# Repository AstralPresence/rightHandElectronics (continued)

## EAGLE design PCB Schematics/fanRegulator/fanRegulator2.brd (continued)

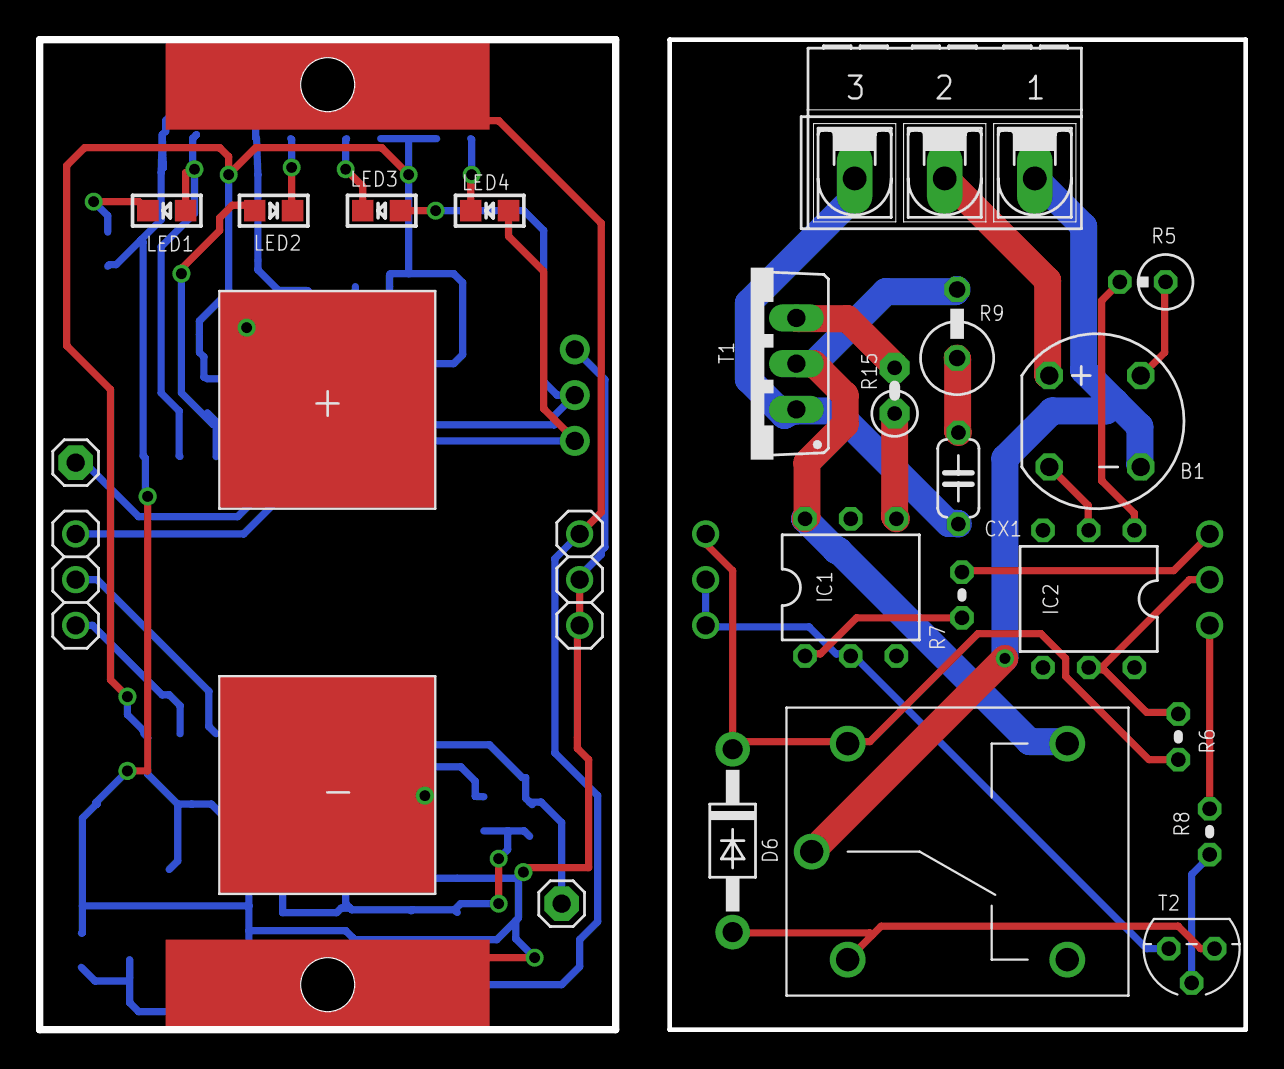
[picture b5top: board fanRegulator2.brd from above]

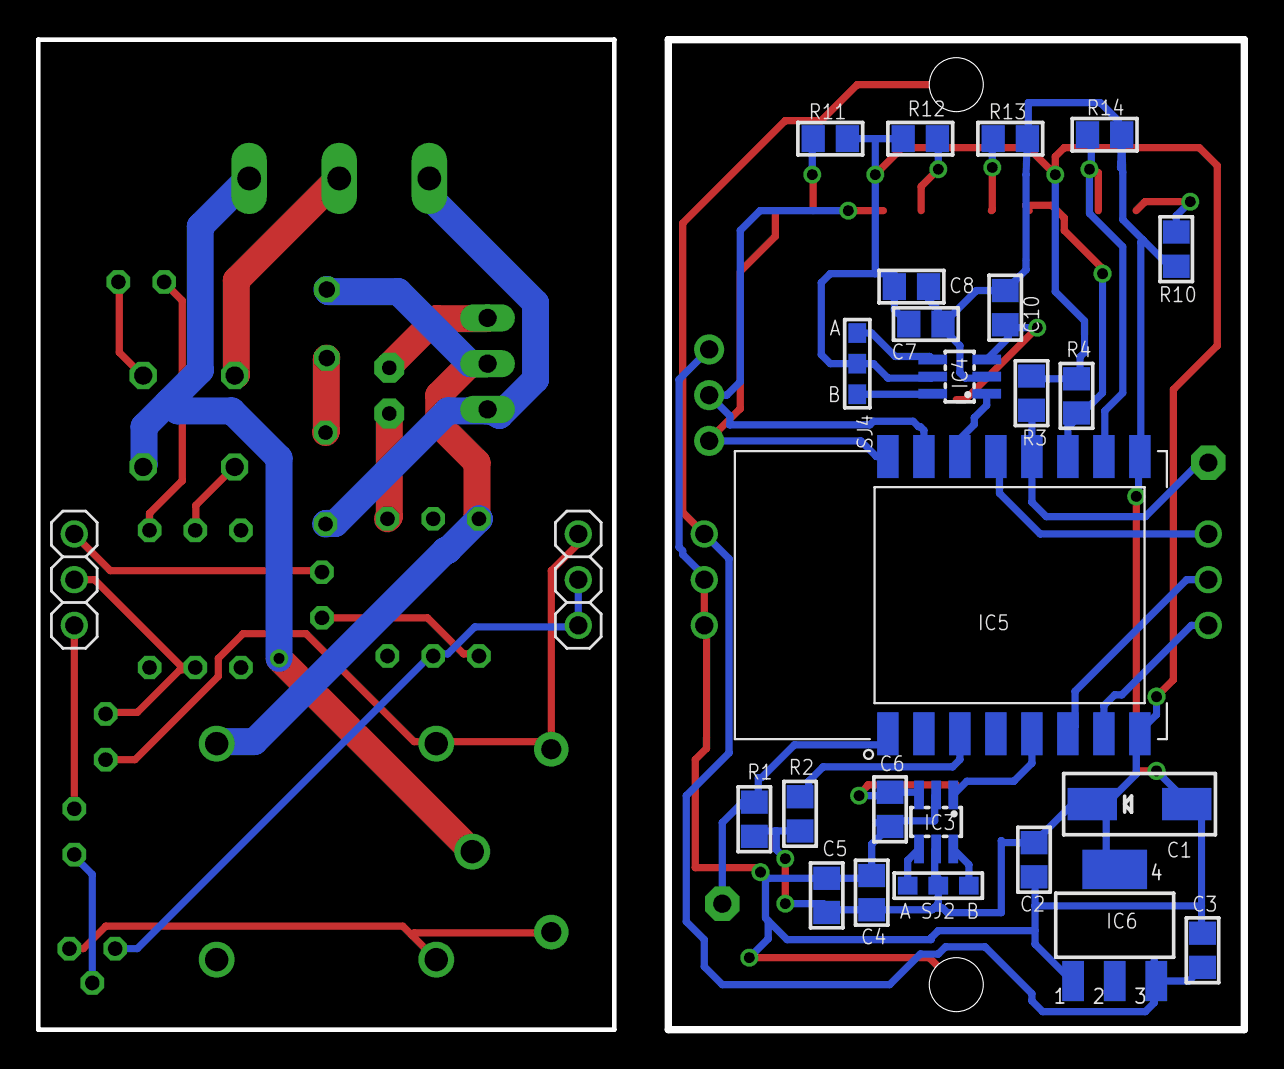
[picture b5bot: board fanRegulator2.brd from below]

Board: 2 copper layers, 66.9 x 55.0 mm, 54 parts (26 on the bottom side), 43 nets.

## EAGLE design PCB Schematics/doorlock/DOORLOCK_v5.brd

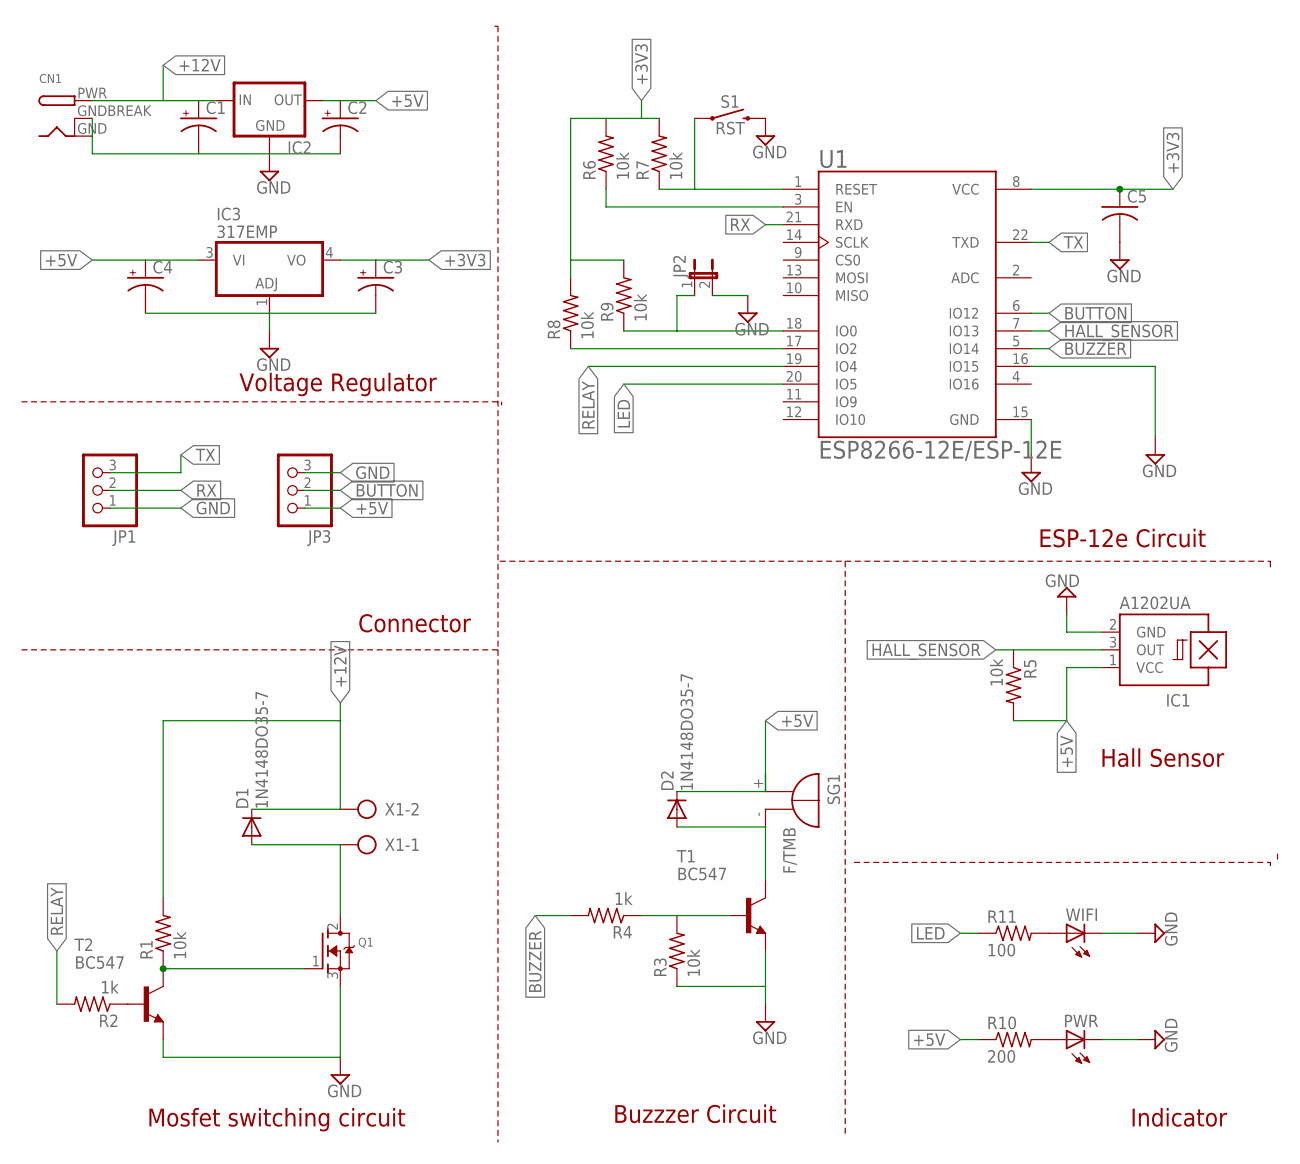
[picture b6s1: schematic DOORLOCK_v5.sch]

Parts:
C1, C2, C3, C4: CPOL-USE2.5-5; E2,5-5
C5: C-US025-030X050; C025-030X050
CN1: DCBARRELPTH; DCJACK_2MM_PTH
D1, D2: 1N4148DO35-7; DO35-7
IC1: A1202UA; SIP3-UA
IC2: 78XXS
IC3: 317EMP; SOT223
JP1, JP3: PINHD-1X3; 1X03
JP2: JP1E; JP1
PWR: LED3MM
Q1: MOSFET-NGDS_TO220V; TO220V
R1, R3, R5, R6, R7, R8, R9: 10k; 0207/2V
R2, R4: 1k; 0207/2V
R10: 200; 0207/2V
R11: 100; 0207/2V
S1: RST; TACTILE_SWITCH_PTH_6.0MM
SG1: F/TMB
T1, T2: BC547; TO92
U1: ESP8266-12E/ESP-12E; XCVR_ESP8266-12E/ESP-12E
WIFI: LED3MM
X1: AK500/2-H

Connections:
+3V3: C3.+, C5.1, IC3.4 (VO), R6.2, R7.2, R8.2, R9.2, U1.8 (VCC)
+5V: C2.+, C4.+, D2.C, IC1.1 (VCC), IC2.OUT, IC3.3 (VI), JP3.1, R5.2, R10.1, SG1.+
+12V: C1.+, CN1.PWR, D1.C, IC2.IN, R1.2, X1.2
BUTTON: JP3.2, U1.6 (IO12)
BUZZER: R4.2, U1.5 (IO14)
GND: C1.-, C2.-, C3.-, C4.-, C5.2, CN1.GND, CN1.GNDBREAK, IC1.2 (GND), IC2.GND, IC3.1 (ADJ), JP1.1, JP2.2, JP3.3, PWR.K (C), Q1.3 (S), R3.1, S1.3 (2), T1.1 (E), T2.1 (E), U1.15 (GND), U1.16 (IO15), WIFI.K (C)
HALL_SENSOR: IC1.3 (OUT), R5.1, U1.7 (IO13)
LED: R11.1, U1.20 (IO5)
unnamed: Q1.1 (G), R1.1, T2.3 (C)
unnamed: D2.A, SG1.-, T1.3 (C)
unnamed: D1.A, Q1.2 (D), X1.1
unnamed: R3.2, R4.1, T1.2 (B)
unnamed: R2.1, T2.2 (B)
unnamed: R8.1, U1.17 (IO2)
unnamed: R7.1, S1.1, U1.1 (RESET)
unnamed: R6.1, U1.3 (EN)
unnamed: JP2.1, R9.1, U1.18 (IO0)
unnamed: PWR.A, R10.2
unnamed: R11.2, WIFI.A
RELAY: R2.2, U1.19 (IO4)
RX: JP1.2, U1.21 (RXD)
TX: JP1.3, U1.22 (TXD)

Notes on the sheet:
Voltage Regulator
Connector
Mosfet switching circuit
Indicator
Hall Sensor
ESP-12e Circuit
Buzzzer Circuit

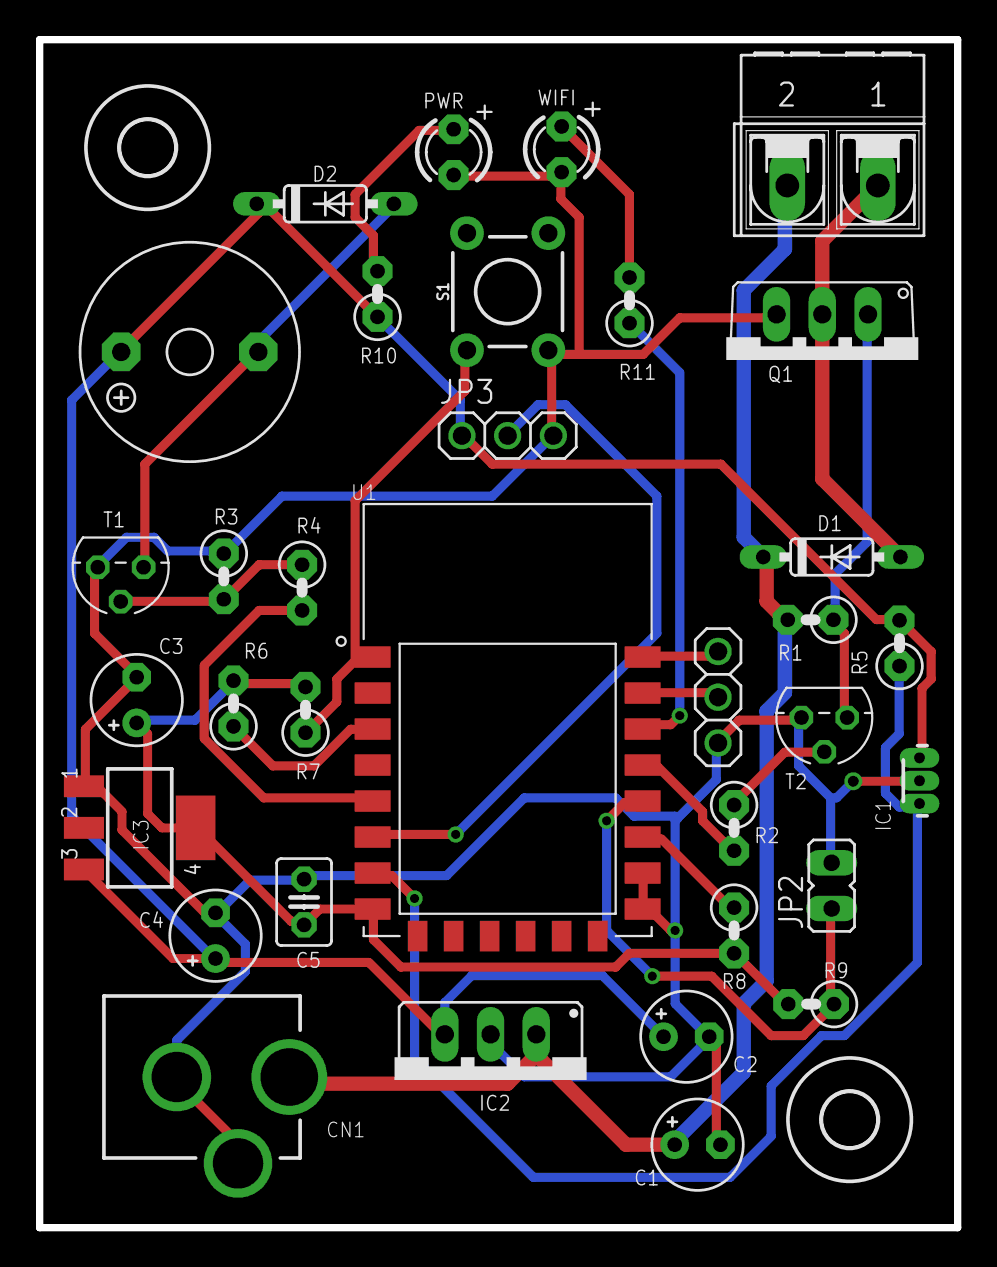
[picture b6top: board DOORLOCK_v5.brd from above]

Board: 2 copper layers, 51.0 x 66.0 mm, 36 parts (0 on the bottom side), 22 nets.

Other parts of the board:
U$1, U$2: MOUNTINGHOLE_3.0

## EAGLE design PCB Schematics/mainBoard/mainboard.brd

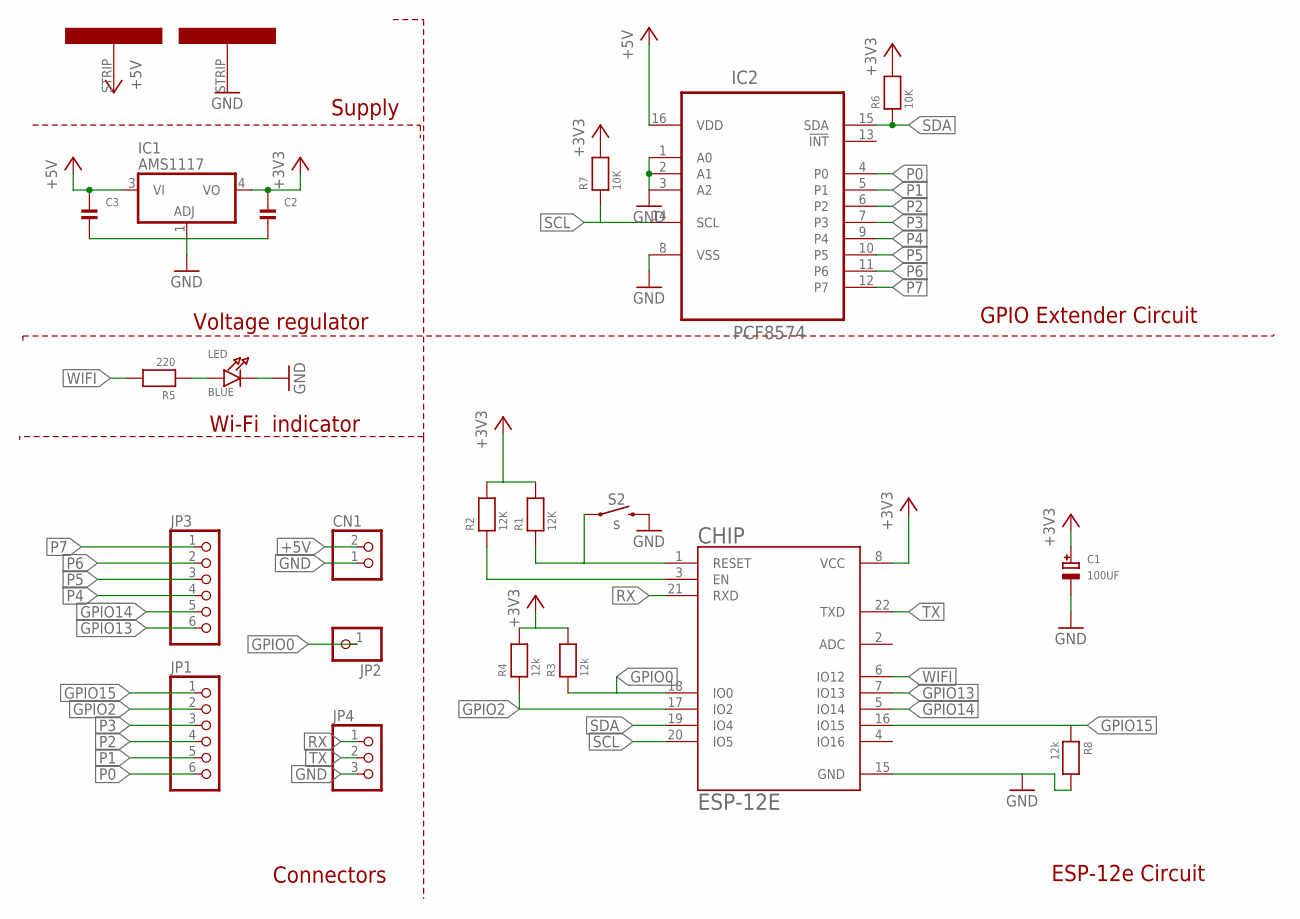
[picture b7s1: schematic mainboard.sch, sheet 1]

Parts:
C1: 100UF; EIA6032-28/C-W
C2, C3: CAP_CERAMIC0805; 0805
CHIP: ESP-12E; XCVR_ESP8266-12E/ESP-12E
CN1: JST_2PIN-THM; JST-PH-2-THM
IC1: AMS1117; SOT223
IC2: PCF8574; SOIC127P1032X265-16N
JP1, JP3: PINHD-1X6CB; 1X06-CLEANBIG
JP2: PINHD-1X1CB; 1X01-CLEANBIG
JP4: PINHD-1X3CB; 1X03-CLEANBIG
LED: BLUE; CHIPLED_0805
R1, R2: 12K; 0805
R3, R4, R8: 12k; 0805
R5: 220; 0805
R6, R7: 10K; 0805
RAIL1: RAIL1; STRIP
RAIL2: RAIL2; STRIP
S2: s; TACTILE_SWITCH_PTH_6.0MM_KIT

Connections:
+3V3: C1.+, C2.1, CHIP.8 (VCC), IC1.4 (VO), R1.2, R2.2, R3.2, R4.2, R6.2, R7.2
+5V: C3.1, CN1.2 (1), IC1.3 (VI), IC2.16 (VDD), RAIL1.STRIP
GND: C1.-, C2.2, C3.2, CHIP.15 (GND), CN1.1 (2), IC1.1 (ADJ), IC2.1 (A0), IC2.2 (A1), IC2.3 (A2), IC2.8 (VSS), JP4.3, LED.C, R8.2, RAIL2.STRIP, S2.3 (2)
GPIO0: CHIP.18 (IO0), JP2.1, R3.1
GPIO2: CHIP.17 (IO2), JP1.2, R4.1
GPIO13: CHIP.7 (IO13), JP3.6
GPIO14: CHIP.5 (IO14), JP3.5
GPIO15: CHIP.16 (IO15), JP1.1, R8.1
unnamed: CHIP.1 (RESET), R1.1, S2.1
unnamed: CHIP.3 (EN), R2.1
unnamed: LED.A, R5.1
P0: IC2.4 (P0), JP1.6
P1: IC2.5 (P1), JP1.5
P2: IC2.6 (P2), JP1.4
P3: IC2.7 (P3), JP1.3
P4: IC2.9 (P4), JP3.4
P5: IC2.10 (P5), JP3.3
P6: IC2.11 (P6), JP3.2
P7: IC2.12 (P7), JP3.1
RX: CHIP.21 (RXD), JP4.1
SCL: CHIP.20 (IO5), IC2.14 (SCL), R7.1
SDA: CHIP.19 (IO4), IC2.15 (SDA), R6.1
TX: CHIP.22 (TXD), JP4.2
WIFI: CHIP.6 (IO12), R5.2

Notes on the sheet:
Voltage regulator
Supply
Wi-Fi indicator
Connectors
ESP-12e Circuit
GPIO Extender Circuit

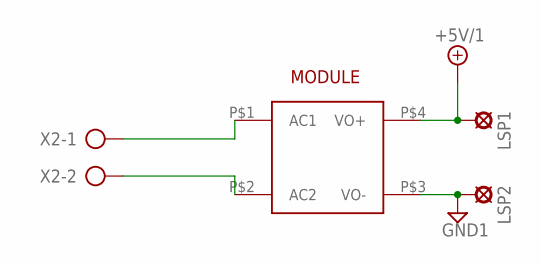
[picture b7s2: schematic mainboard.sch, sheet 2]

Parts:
LSP1, LSP2: LSP10
MODULE: HLK-PM01
X2: AK500/2-H

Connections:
+5V/1: LSP1.MP, MODULE.P$4 (VO+)
GND1: LSP2.MP, MODULE.P$3 (VO-)
unnamed: MODULE.P$1 (AC1), X2.1
unnamed: MODULE.P$2 (AC2), X2.2

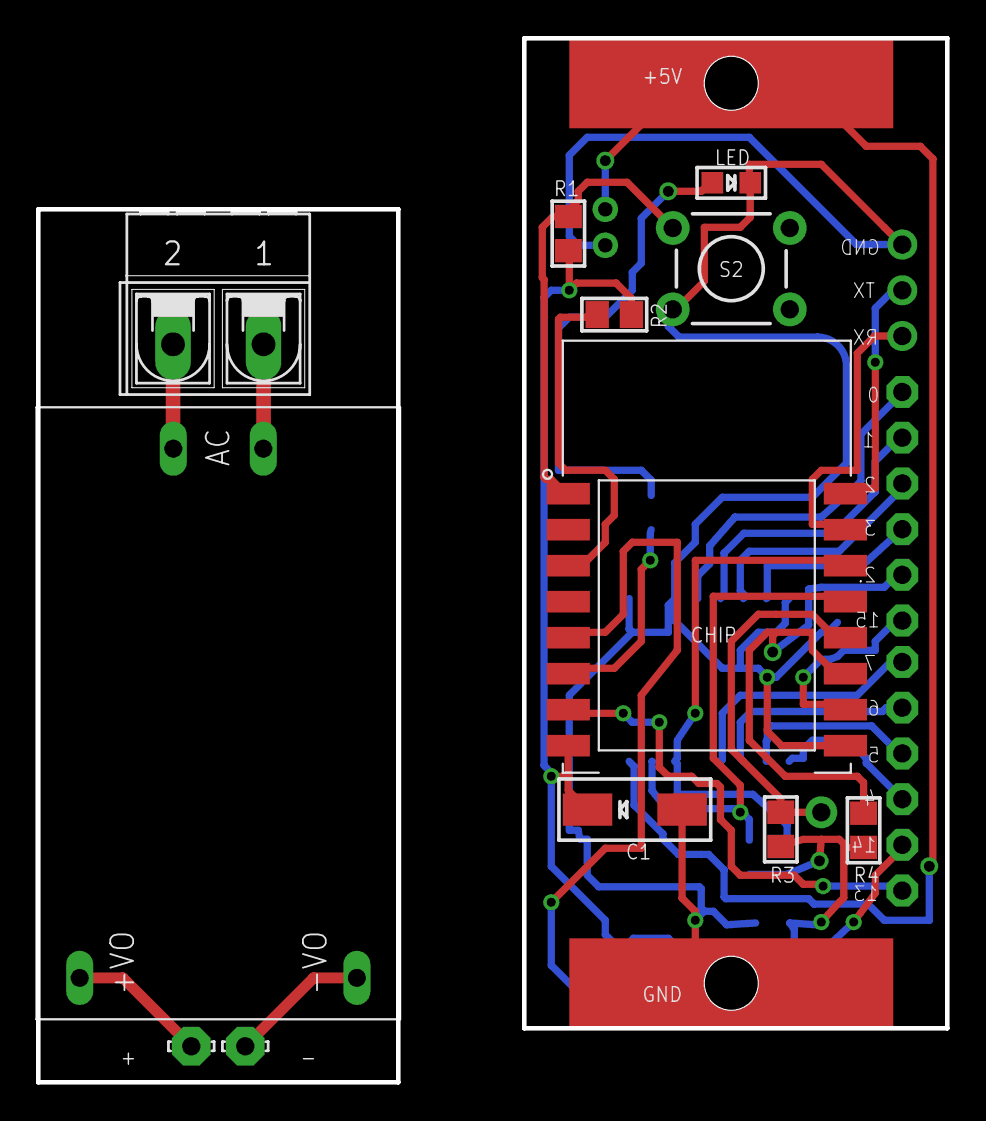
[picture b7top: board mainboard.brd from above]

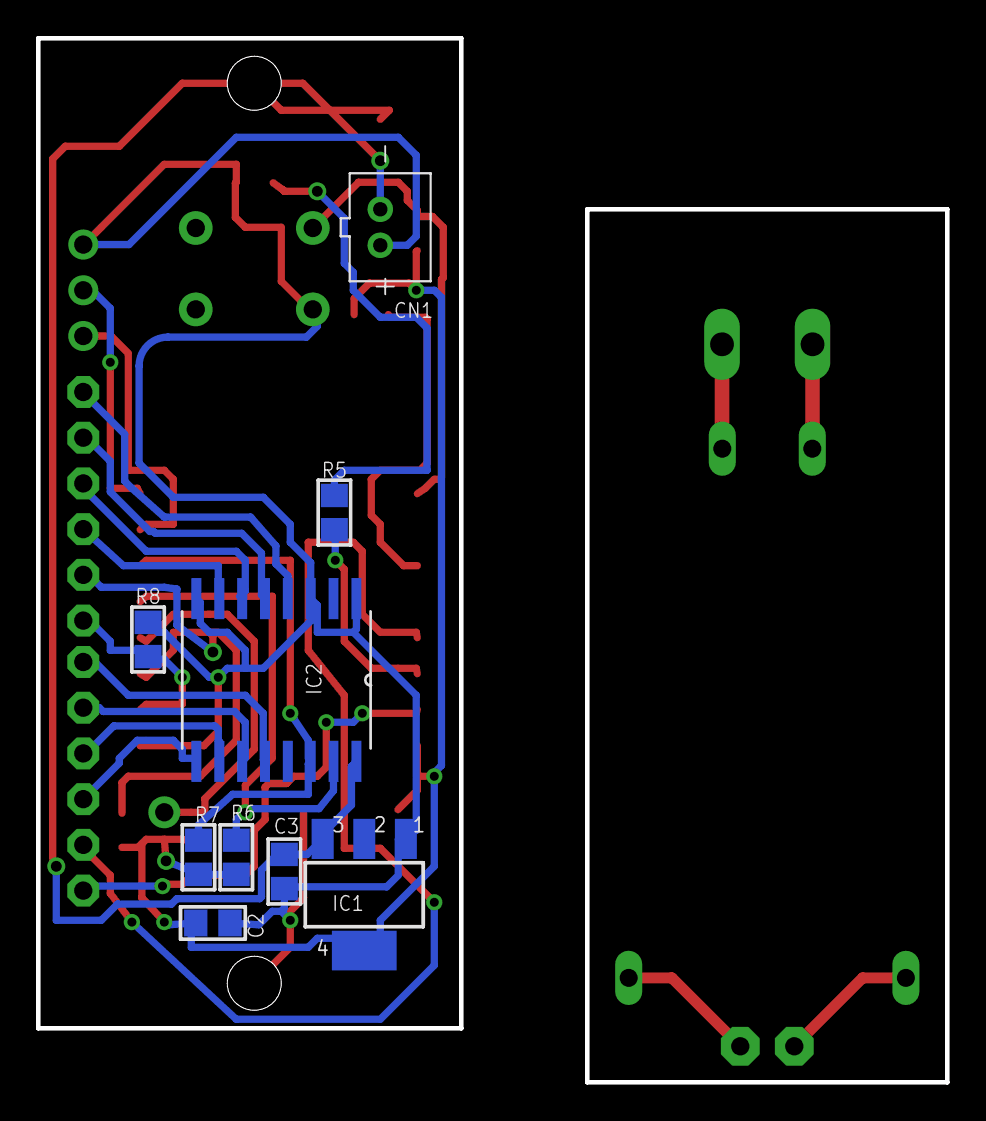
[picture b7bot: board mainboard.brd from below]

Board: 2 copper layers, 50.5 x 58.0 mm, 27 parts (9 on the bottom side), 28 nets.

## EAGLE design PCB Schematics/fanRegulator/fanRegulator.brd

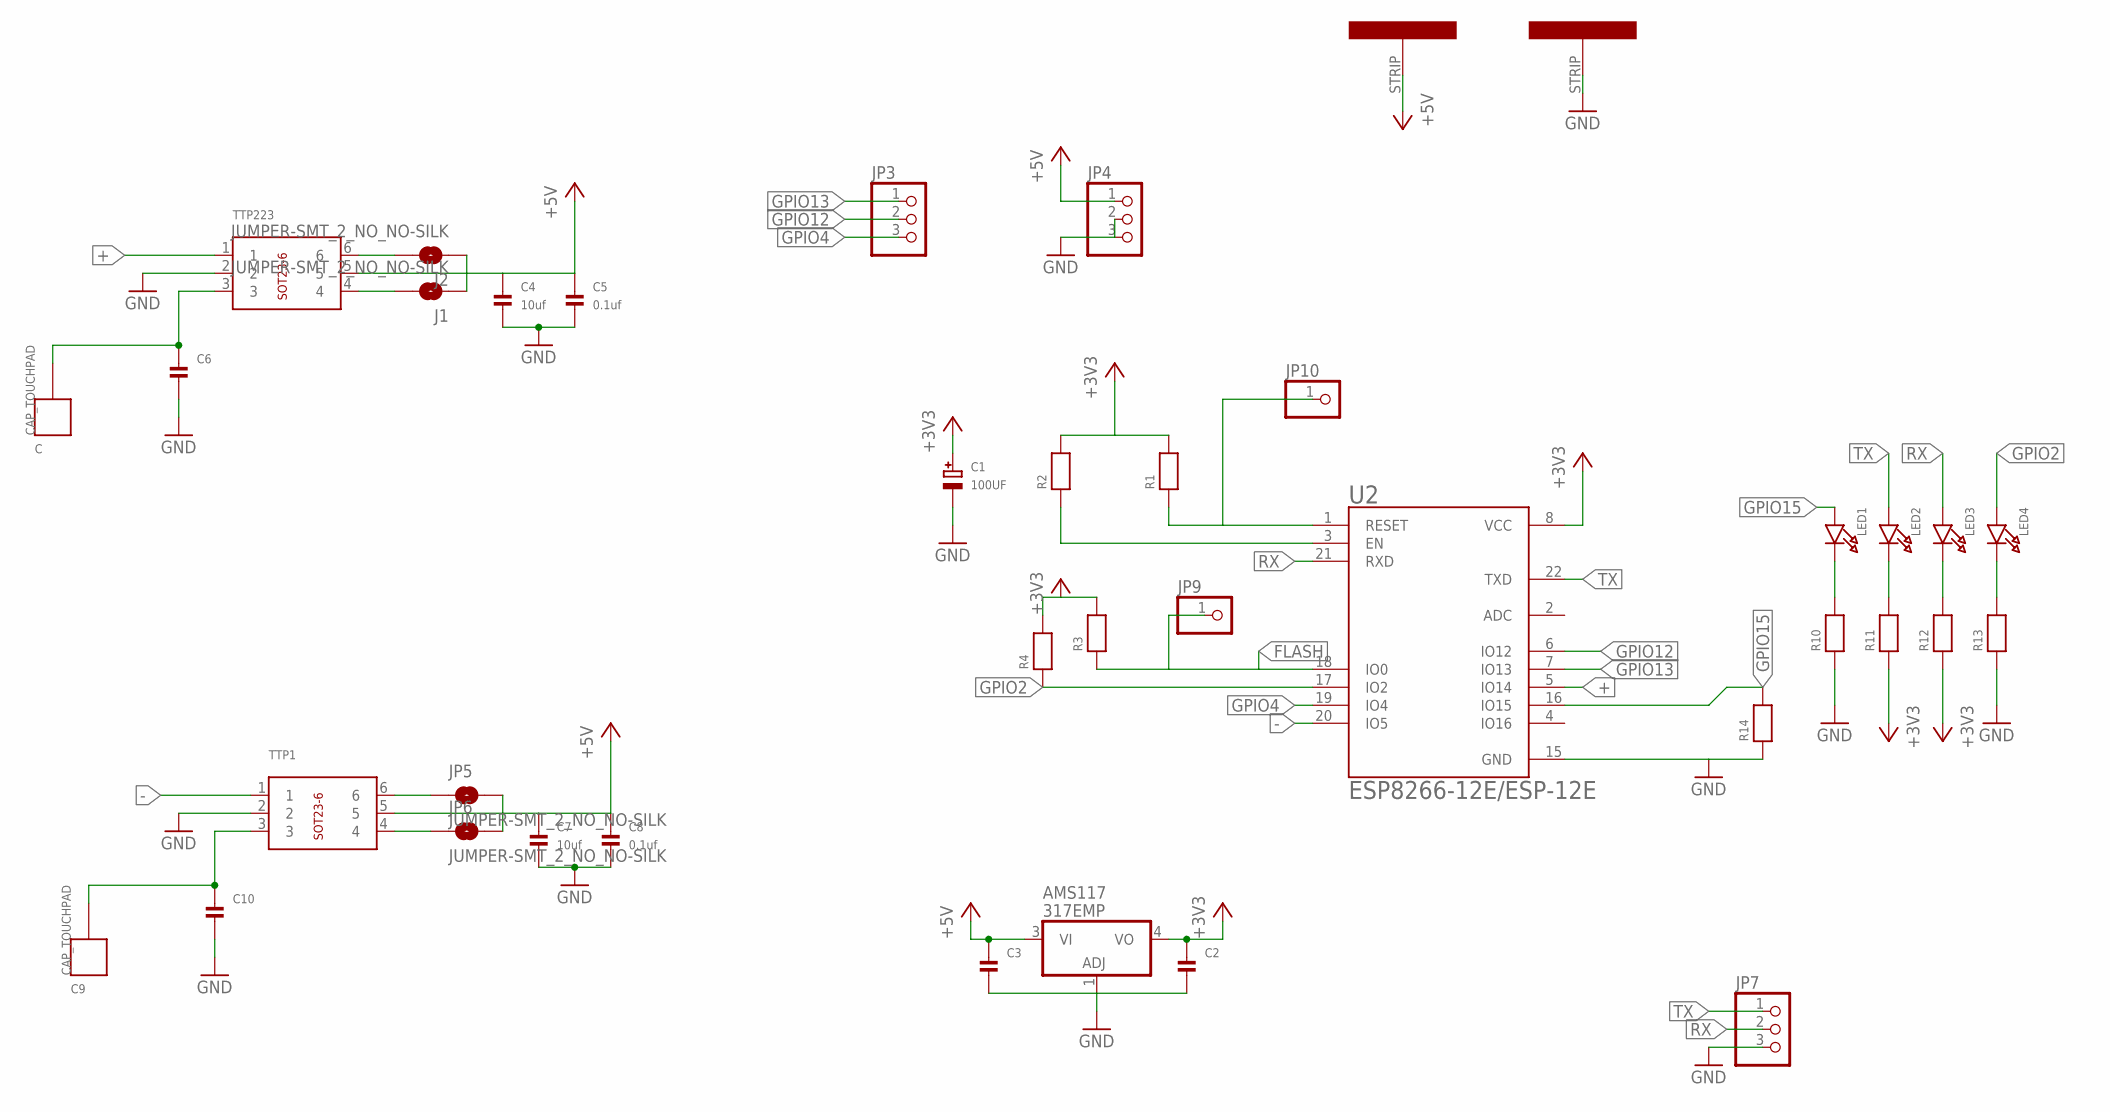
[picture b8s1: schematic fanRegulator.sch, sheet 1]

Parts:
AMS117: 317EMP; SOT223
C, C9: CAP_TOUCHPAD
C1: 100UF; EIA6032-28/C-W
C2, C3, C6, C10: CAP_CERAMIC0805; 0805
C4, C7: 10uf; 0805
C5, C8: 0.1uf; 0805
J1, J2: JUMPER-SMT_2_NO_NO-SILK; SMT-JUMPER_2_NO_NO-SILK
JP3, JP4: PINHD-1X3; 1X03
JP5, JP6: JUMPER-SMT_2_NO_NO-SILK; SMT-JUMPER_2_NO_NO-SILK
JP7: PINHD-1X3CB; 1X03-CLEANBIG
JP9, JP10: PINHD-1X1; 1X01
LED1, LED2, LED3, LED4: LED0805; CHIPLED_0805
R1, R2, R3, R4, R10, R11, R12, R13, R14: RESISTOR0805; 0805
TTP1, TTP223: BREAKOUT_SOT23-6
U2: ESP8266-12E/ESP-12E; XCVR_ESP8266-12E/ESP-12E
U$2, U$3: STRIP

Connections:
+: TTP223.1, U2.5 (IO14)
+3V3: AMS117.4 (VO), C1.+, C2.1, R1.2, R2.2, R3.2, R4.2, R11.1, R12.1, U2.8 (VCC)
+5V: AMS117.3 (VI), C3.1, C4.1, C5.1, C7.1, C8.1, J1.1, J2.1, JP4.1, JP5.2, JP6.2, TTP1.5, TTP223.5, U$2.STRIP
-: TTP1.1, U2.20 (IO5)
FLASH: JP9.1, R3.1, U2.18 (IO0)
GND: AMS117.1 (ADJ), C1.-, C2.2, C3.2, C4.2, C5.2, C6.2, C7.2, C8.2, C10.2, JP4.2, JP4.3, JP7.3, R10.1, R13.1, R14.1, TTP1.2, TTP223.2, U2.15 (GND), U$3.STRIP
GPIO2: LED4.A, R4.1, U2.17 (IO2)
GPIO4: JP3.3, U2.19 (IO4)
GPIO12: JP3.2, U2.6 (IO12)
GPIO13: JP3.1, U2.7 (IO13)
GPIO15: LED1.A, R14.2, U2.16 (IO15)
unnamed: C.P$1, C6.1, TTP223.3
unnamed: JP10.1, R1.1, U2.1 (RESET)
unnamed: R2.1, U2.3 (EN)
unnamed: J2.2, TTP223.6
unnamed: J1.2, TTP223.4
unnamed: C9.P$1, C10.1, TTP1.3
unnamed: JP5.1, TTP1.6
unnamed: JP6.1, TTP1.4
unnamed: LED1.C, R10.2
unnamed: LED2.C, R11.2
unnamed: LED3.C, R12.2
unnamed: LED4.C, R13.2
RX: JP7.2, LED3.A, U2.21 (RXD)
TX: JP7.1, LED2.A, U2.22 (TXD)

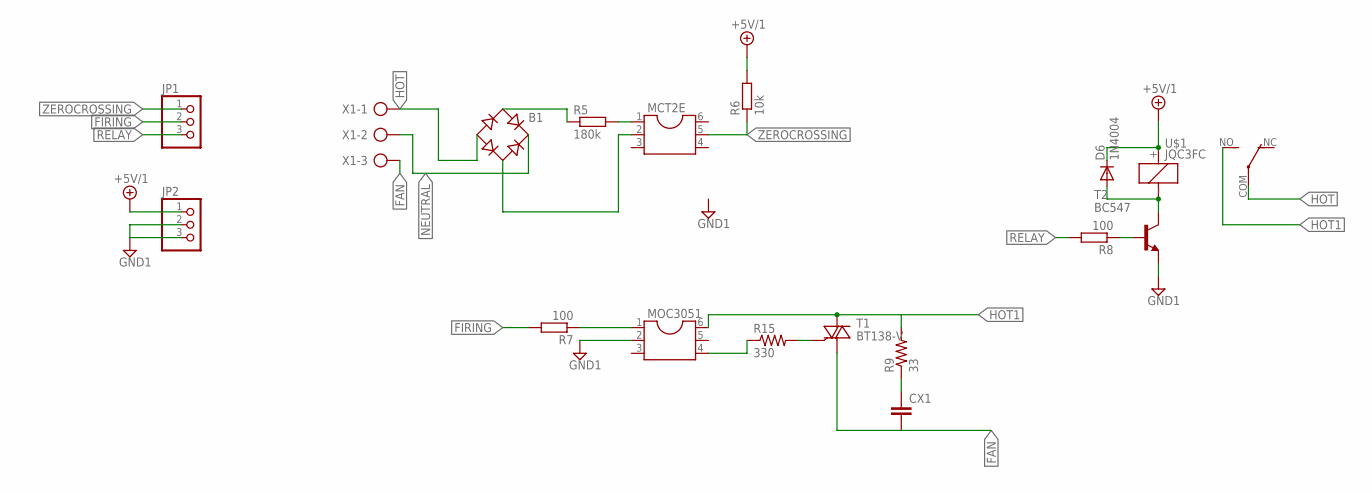
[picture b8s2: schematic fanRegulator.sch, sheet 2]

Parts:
B1: RB1A
CX1: C-EU050-024X044; C050-024X044
D6: 1N4004; DO41-10
JP1, JP2: PINHD-1X3; 1X03
MCT2E: DIL6; DIL06
MOC3051: DIL6; DIL06
R5: 180k; 0309V
R6: 10k; 0204V
R7, R8: 100; 0204V
R9: 33; 0411V
R15: 330; 0207/2V
T1: BT138-V; TO220BV
T2: BC547; TO92
U$1: JQC3FC
X1: AK500/3-H

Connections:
+5V/1: D6.C, JP2.1, R6.2, U$1.+
FAN: CX1.2, T1.T1 (A1), X1.3
FIRING: JP1.2, R7.2
GND1: JP2.2, JP2.3, MOC3051.2, T2.1 (E)
HOT: B1.-, U$1.COM, X1.1
HOT1: MOC3051.6, R9.2, T1.T2 (A2), U$1.NO
unnamed: B1.AC1, R5.1
unnamed: B1.AC2, MCT2E.2
unnamed: MCT2E.1, R5.2
unnamed: MOC3051.1, R7.1
unnamed: MOC3051.4, R15.1
unnamed: R15.2, T1.G
unnamed: CX1.1, R9.1
unnamed: D6.A, T2.3 (C), U$1._ (-)
unnamed: R8.1, T2.2 (B)
NEUTRAL: B1.+, X1.2
RELAY: JP1.3, R8.2
ZEROCROSSING: JP1.1, MCT2E.5, R6.1

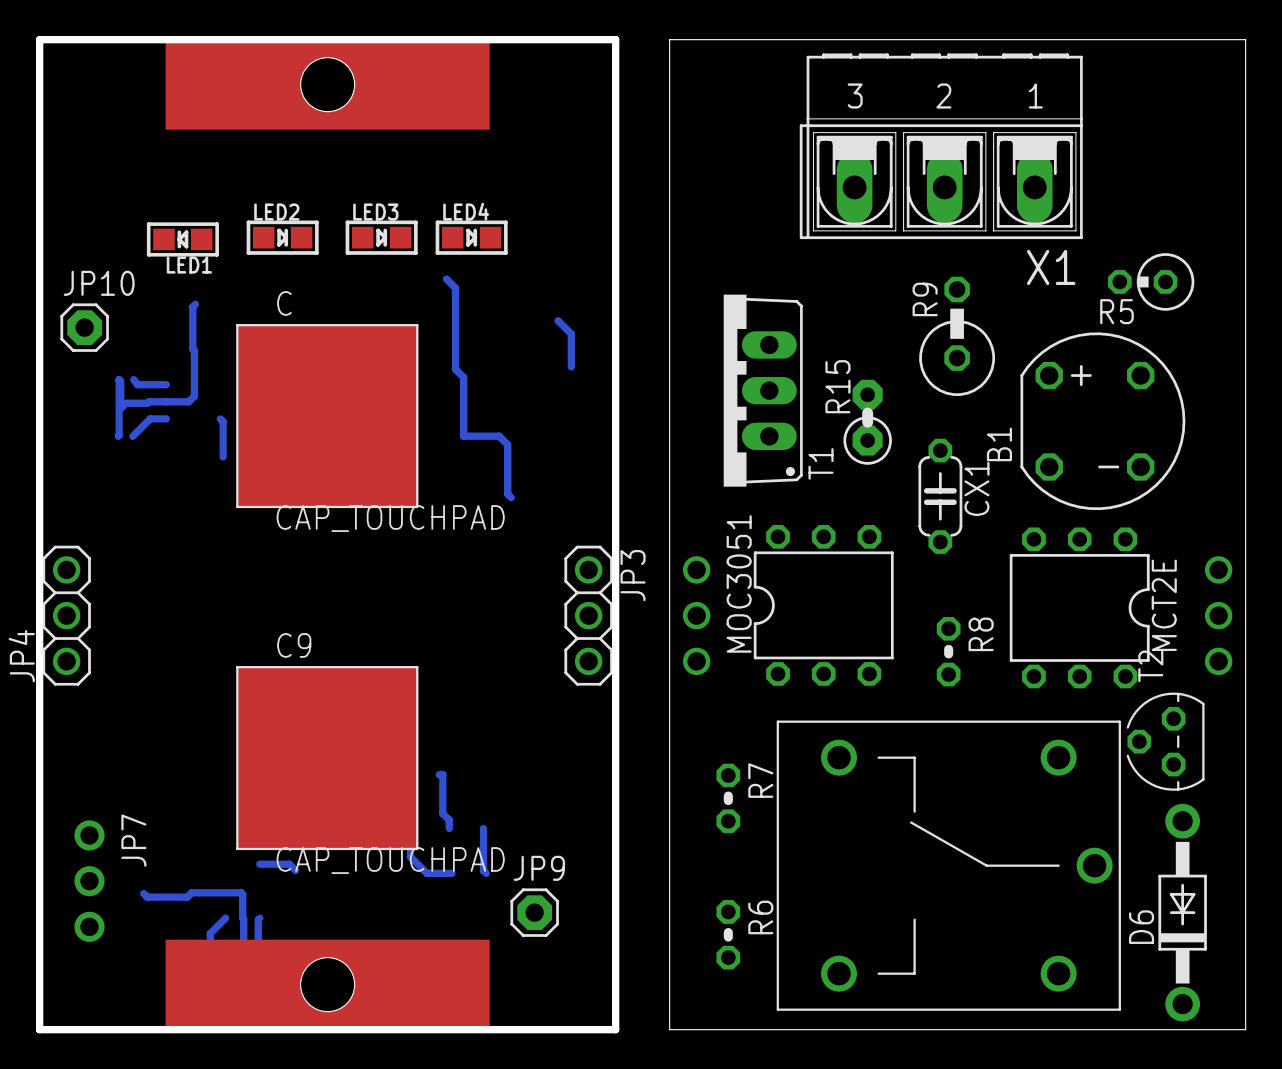
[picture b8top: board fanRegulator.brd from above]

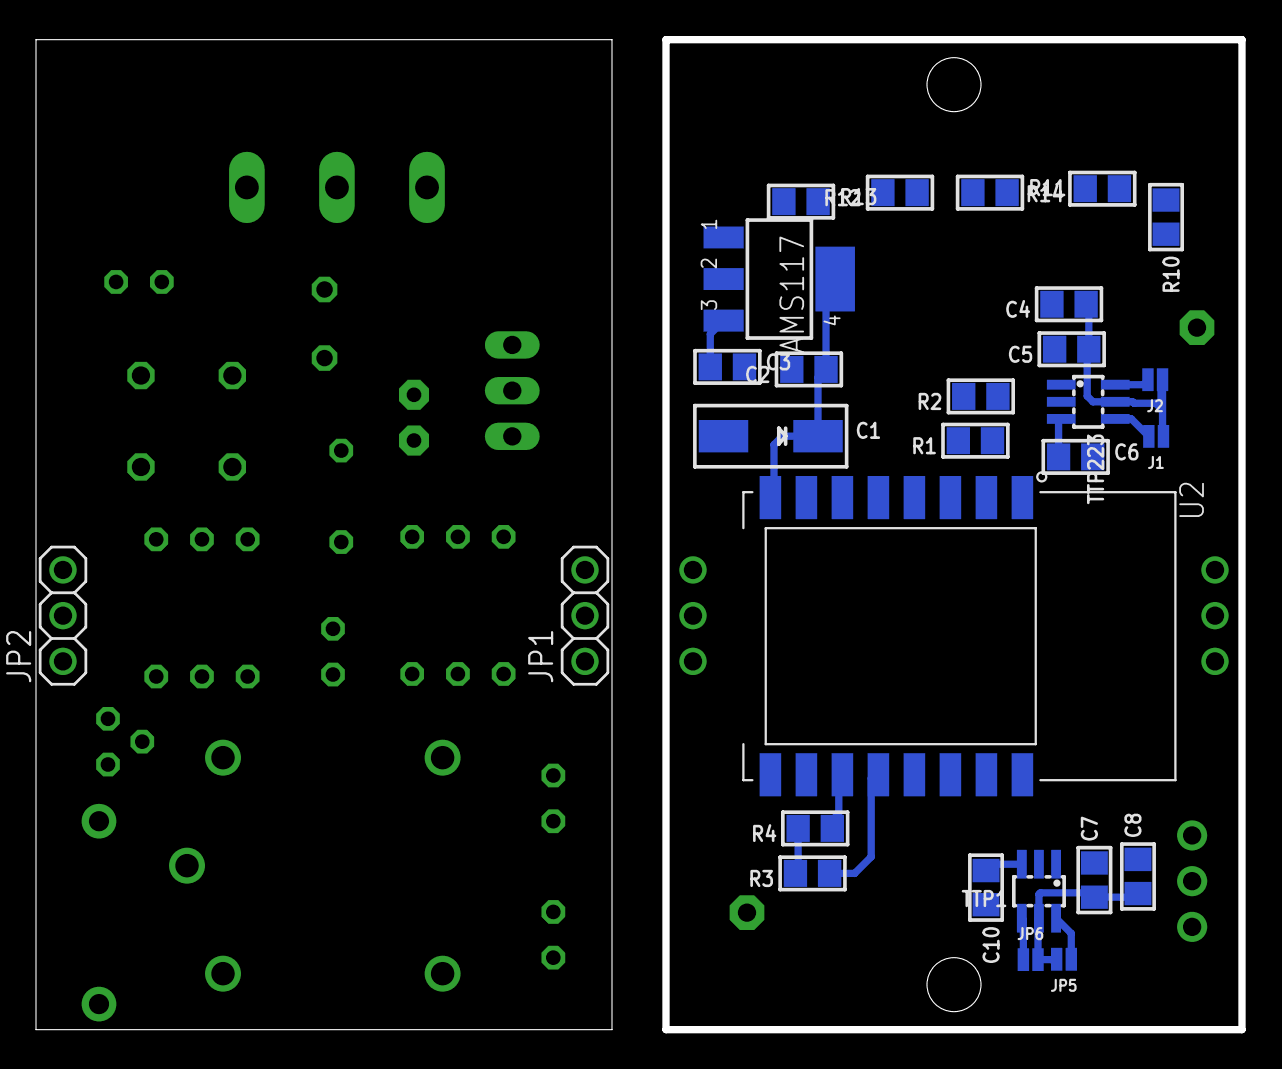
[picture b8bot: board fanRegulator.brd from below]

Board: 2 copper layers, 66.8 x 55.0 mm, 56 parts (28 on the bottom side), 43 nets.

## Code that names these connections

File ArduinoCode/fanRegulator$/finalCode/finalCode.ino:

#include <ESP8266WiFi.h>
#include <Ticker.h>
#include <AsyncMqttClient.h>
#include <ArduinoJson.h>

const char* TOPIC = "college/office/fan";


#define WIFI_SSID  "Astral Presence"
#define WIFI_PASSWORD  "AstralDev108"

//#define WIFI_SSID "crazybee"
//#define WIFI_PASSWORD "12345678"


#define MQTT_HOST IPAddress(192,168,1,110)

//#define MQTT_HOST "www.mqtt-dashboard.com"
#define MQTT_PORT 1883

#define led1 15
#define led2 2
#define led3 3
#define led4 1
#define plus 5
#define minus 14
#define zcPin 12
#define firePin 4
#define relay 13



#define Step 1125 //microseconds
#define offset 200

AsyncMqttClient mqttClient;
Ticker mqttReconnectTimer;
WiFiEventHandler wifiConnectHandler;
WiFiEventHandler wifiDisconnectHandler;
Ticker wifiReconnectTimer;
Ticker sendTimer;

bool countChanged = false; 
int time1,time2;
int count = 0;
int x,y;
int fireTime;
int led[4][9]= {
              {0,150,1024,1024,1024,1024,1024,1024,1024},
               { 0,0,0,150,1024,1024,1024,1024,1024},
               { 1024,1024,1024,1024,1024,876,0,0,0},
                {1024,1024,1024,1024,1024,1024,1024,876,0}
            };




void connectToWifi() {                        
  Serial.println("Connecting to Wi-Fi...");
  WiFi.begin(WIFI_SSID, WIFI_PASSWORD);
}

void onWifiConnect(const WiFiEventStationModeGotIP& event) {
  Serial.println("Connected to Wi-Fi.");
  connectToMqtt();  
}

void onWifiDisconnect(const WiFiEventStationModeDisconnected& event) {
  Serial.println("Disconnected from Wi-Fi.");
  mqttReconnectTimer.detach(); // ensure we don't reconnect to MQTT while reconnecting to Wi-Fi
  
  wifiReconnectTimer.once(2, connectToWifi);
}

void connectToMqtt() {
 Serial.println("Connecting to MQTT...");
  mqttClient.connect();
}

void onMqttConnect(bool sessionPresent){
  Serial.println("Connected to MQTT.");
  mqttClient.subscribe(TOPIC, 0);
} 

void onMqttDisconnect(AsyncMqttClientDisconnectReason reason){
  Serial.println("Disconnected from MQTT.");
 if (WiFi.isConnected()){
    mqttReconnectTimer.once(2, connectToMqtt);
  }
}

void onMqttMessage(char* topic, char* payload, AsyncMqttClientMessageProperties properties, size_t len, size_t index, size_t total) {


const size_t capacity = JSON_OBJECT_SIZE(1) + 20;
DynamicJsonBuffer jsonBuffer(capacity);
JsonObject& root = jsonBuffer.parseObject(payload);
int speed = root["state"].as<int>();
 


  
if(speed==0){count=0  ;}
else if(speed == 100){count = 8;} 
else
 count = (speed/12.5) + 1;

 setLed(count);
 setspeed(count);
 }


void setup() {
 
 wifiConnectHandler = WiFi.onStationModeGotIP(onWifiConnect);
  wifiDisconnectHandler = WiFi.onStationModeDisconnected(onWifiDisconnect);
  mqttClient.onConnect(onMqttConnect);
  mqttClient.onDisconnect(onMqttDisconnect);
  mqttClient.onMessage(onMqttMessage);
  mqttClient.setServer(MQTT_HOST, MQTT_PORT);

  connectToWifi();


  pinMode(plus,INPUT);
  pinMode(minus,INPUT);
  pinMode(firePin,OUTPUT);
   pinMode(relay,OUTPUT);
   setLed(0);
   OFF();
   time1 = millis();
   time2 = millis();


}

void loop() {


if(millis()-time1>150){ 
x = digitalRead(plus);
y = digitalRead(minus);

if(x){
  
   if(count<8){
  count = count + 1;
sendTimer.detach();
sendTimer.once_ms(200,sendSpeed);
  
  setLed(count);
  setspeed(count);
  
   }
  }else if(y){
    if(count>0){
    count = count-1;
  sendTimer.detach();
   sendTimer.once_ms(200,sendSpeed); 
    setLed(count);
    setspeed(count);
    
    }
    }
  time1= millis();
 }


  
  
 if(count!=0){ 
if(digitalRead(zcPin)){
pulse();
}}

}


void pulse(){
 
  delayMicroseconds(offset+fireTime);
  digitalWrite(firePin, HIGH);
  delayMicroseconds(80);
  digitalWrite(firePin,LOW);
 
 }


void setLed(int count){
    analogWrite(led1,led[0][count]);
    analogWrite(led2,led[1][count]);
    analogWrite(led3,led[2][count]);
    analogWrite(led4,led[3][count]);
 }

void setspeed(int count){
  if(count==0){
    OFF();
    } else {
      ON();
  fireTime = int((-count*8000+71000)/7);
  Serial.println(fireTime);
  }
  
  }


  
void OFF(){
   digitalWrite(relay,HIGH);
  }

  void ON(){
    
    digitalWrite(relay,LOW);
    
    }

    void sendSpeed(){
      char msg[20];
     sprintf(msg,"%s:%i}","{\"state\"",count*12);
       mqttClient.publish(TOPIC, 0, false, msg);
      
      }

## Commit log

2019-04-02 Added Read Me
2019-04-02 Create smokeDetector
2019-04-02 commit message
